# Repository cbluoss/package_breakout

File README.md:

# Chip package breakout board
A simple breakout pcb for different chip packages

Currently supported packages:
* TSOP-I-56
* TSOP-II-54
* SOIC-28
* LFCSP-8
* MSOP-16
* QSOP-24
* DIP-28

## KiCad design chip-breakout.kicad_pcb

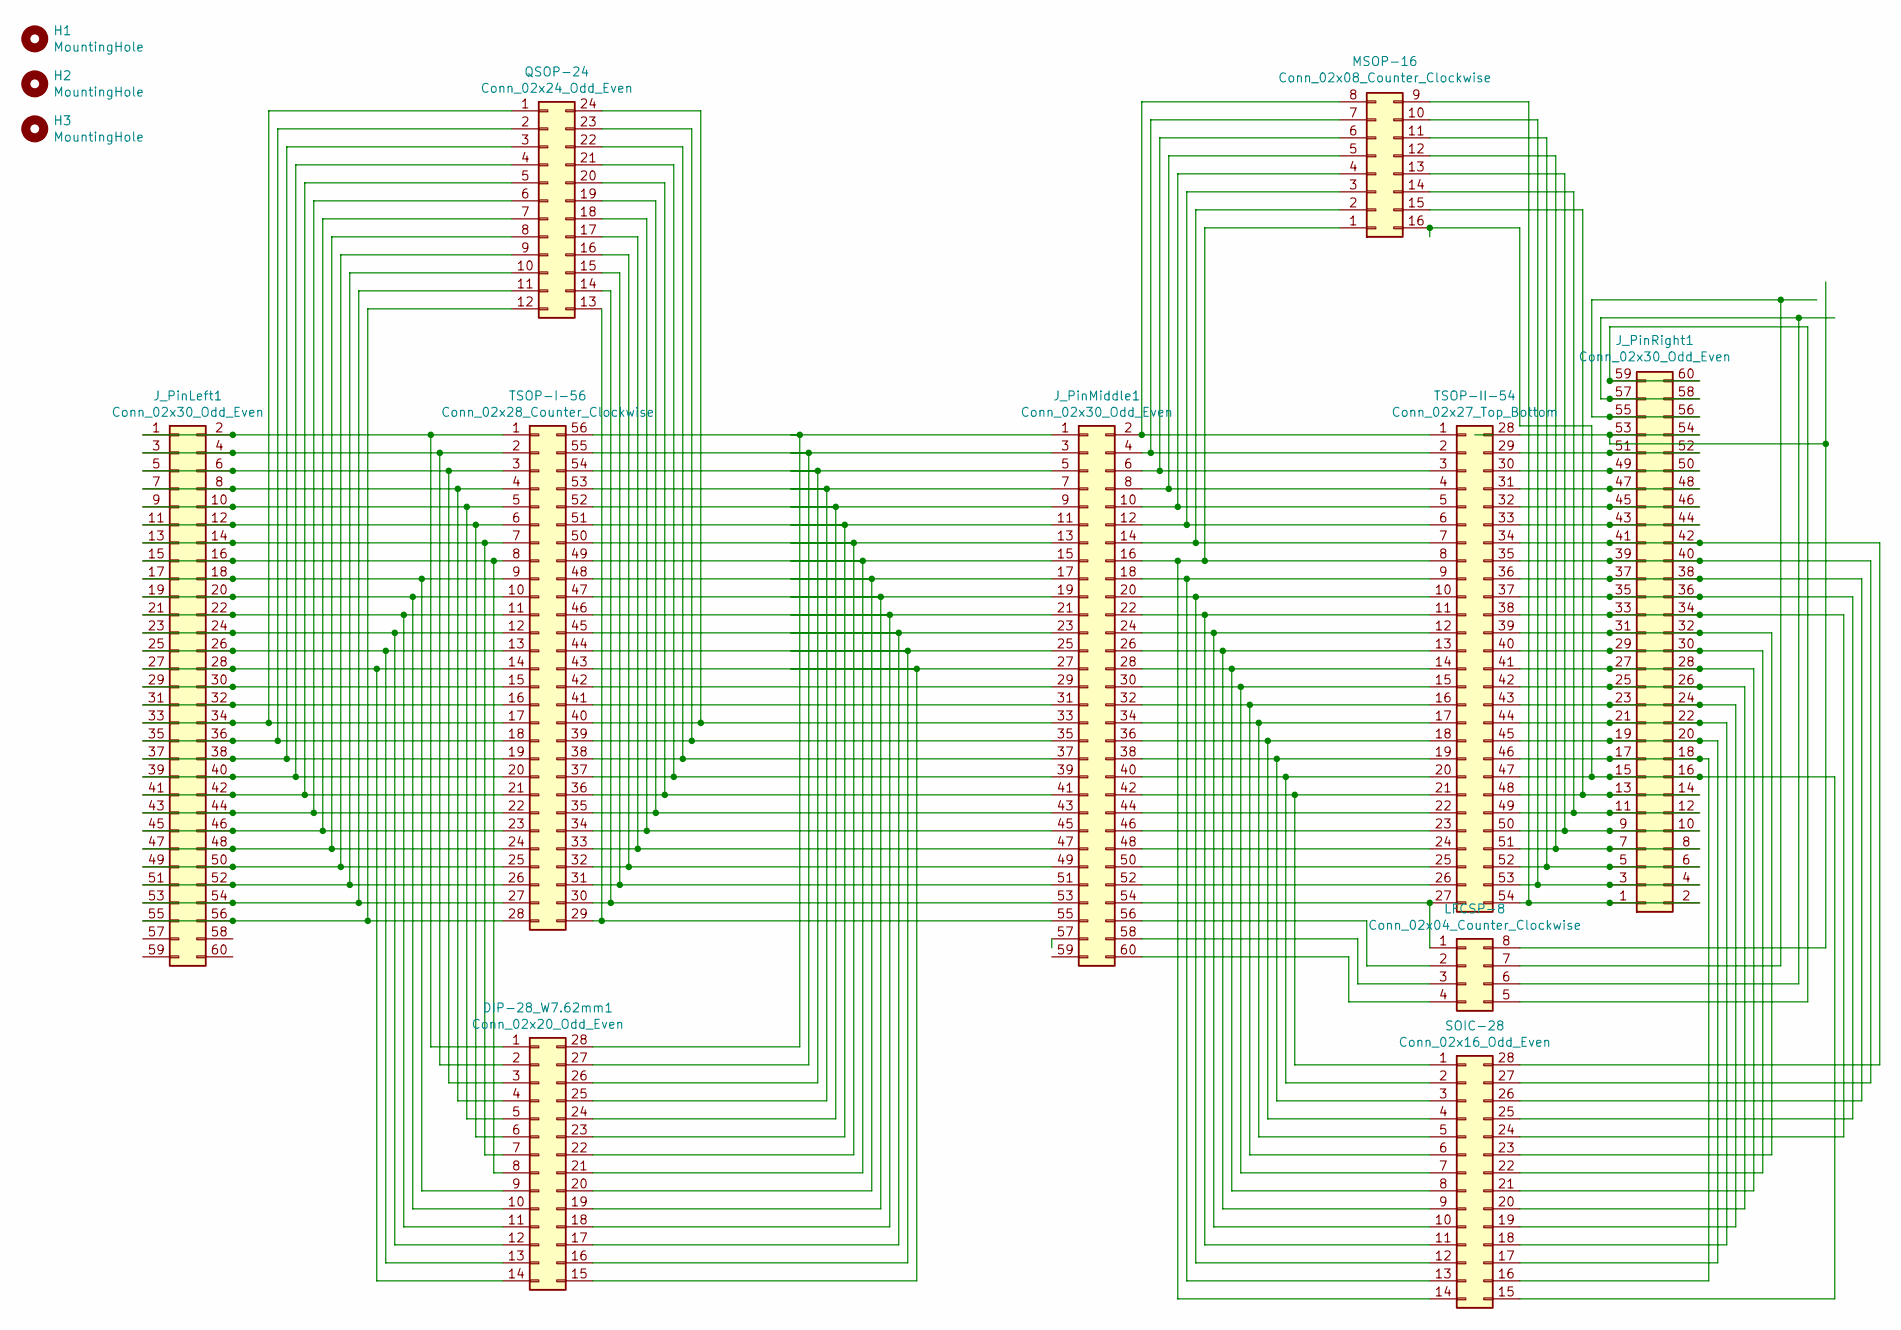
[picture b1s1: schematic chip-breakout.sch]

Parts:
DIP-28_W7.62mm1: Conn_02x20_Odd_Even; DIP-28_W7.62mm_LongPads
H1, H2, H3: MountingHole; MountingHole_3.2mm_M3_ISO7380
J_PinLeft1: Conn_02x30_Odd_Even; PinHeader_2x30_P2.54mm_Vertical
J_PinMiddle1: Conn_02x30_Odd_Even; PinHeader_2x30_P2.54mm_Vertical
J_PinRight1: Conn_02x30_Odd_Even; PinHeader_2x30_P2.54mm_Vertical
LFCSP-8: Conn_02x04_Counter_Clockwise; LFCSP-8-1EP_3x3mm_P0.5mm_EP1.45x1.74mm
MSOP-16: Conn_02x08_Counter_Clockwise; MSOP-16_3x4.039mm_P0.5mm
QSOP-24: Conn_02x24_Odd_Even; QSOP-24_3.9x8.7mm_P0.635mm
SOIC-28: Conn_02x16_Odd_Even; SOIC-28W_7.5x18.7mm_P1.27mm
TSOP-I-56: Conn_02x28_Counter_Clockwise; TSOP-I-56_18.4x14mm_P0.5mm
TSOP-II-54: Conn_02x27_Top_Bottom; TSOP-II-54_22.2x10.16mm_P0.8mm

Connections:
unnamed 0: DIP-28_W7.62mm1.1, J_PinLeft1.1, J_PinLeft1.2, TSOP-I-56.1; also elsewhere on the board
unnamed 1: DIP-28_W7.62mm1.2, J_PinLeft1.3, J_PinLeft1.4, TSOP-I-56.2; also elsewhere on the board
unnamed 2: DIP-28_W7.62mm1.3, J_PinLeft1.5, J_PinLeft1.6, TSOP-I-56.3; also elsewhere on the board
unnamed 3: DIP-28_W7.62mm1.4, J_PinLeft1.7, J_PinLeft1.8, TSOP-I-56.4; also elsewhere on the board
unnamed 4: DIP-28_W7.62mm1.5, J_PinLeft1.9, J_PinLeft1.10, TSOP-I-56.5; also elsewhere on the board
unnamed 5: DIP-28_W7.62mm1.6, J_PinLeft1.11, J_PinLeft1.12, TSOP-I-56.6; also elsewhere on the board
unnamed 6: DIP-28_W7.62mm1.7, J_PinLeft1.13, J_PinLeft1.14, TSOP-I-56.7; also elsewhere on the board
unnamed 7: DIP-28_W7.62mm1.8, J_PinLeft1.15, J_PinLeft1.16, TSOP-I-56.8; also elsewhere on the board
unnamed 8: DIP-28_W7.62mm1.9, J_PinLeft1.17, J_PinLeft1.18, TSOP-I-56.9; also elsewhere on the board
unnamed 9: DIP-28_W7.62mm1.10, J_PinLeft1.19, J_PinLeft1.20, TSOP-I-56.10; also elsewhere on the board
unnamed 10: DIP-28_W7.62mm1.11, J_PinLeft1.21, J_PinLeft1.22, TSOP-I-56.11; also elsewhere on the board
unnamed 11: DIP-28_W7.62mm1.12, J_PinLeft1.23, J_PinLeft1.24, TSOP-I-56.12; also elsewhere on the board
unnamed 12: DIP-28_W7.62mm1.13, J_PinLeft1.25, J_PinLeft1.26, TSOP-I-56.13; also elsewhere on the board
unnamed 13: DIP-28_W7.62mm1.14, J_PinLeft1.27, J_PinLeft1.28, TSOP-I-56.14; also elsewhere on the board
unnamed 14: DIP-28_W7.62mm1.15, J_PinMiddle1.27, TSOP-I-56.43; also elsewhere on the board
unnamed 15: DIP-28_W7.62mm1.16, J_PinMiddle1.25, TSOP-I-56.44; also elsewhere on the board
unnamed 16: DIP-28_W7.62mm1.17, J_PinMiddle1.23, TSOP-I-56.45; also elsewhere on the board
unnamed 17: DIP-28_W7.62mm1.18, J_PinMiddle1.21, TSOP-I-56.46; also elsewhere on the board
unnamed 18: DIP-28_W7.62mm1.19, J_PinMiddle1.19, TSOP-I-56.47; also elsewhere on the board
unnamed 19: DIP-28_W7.62mm1.20, J_PinMiddle1.17, TSOP-I-56.48; also elsewhere on the board
unnamed 20: DIP-28_W7.62mm1.21, J_PinMiddle1.15, TSOP-I-56.49; also elsewhere on the board
unnamed 21: DIP-28_W7.62mm1.22, J_PinMiddle1.13, TSOP-I-56.50; also elsewhere on the board
unnamed 22: DIP-28_W7.62mm1.23, J_PinMiddle1.11, TSOP-I-56.51; also elsewhere on the board
unnamed 23: DIP-28_W7.62mm1.24, J_PinMiddle1.9, TSOP-I-56.52; also elsewhere on the board
unnamed 24: DIP-28_W7.62mm1.25, J_PinMiddle1.7, TSOP-I-56.53; also elsewhere on the board
unnamed 25: DIP-28_W7.62mm1.26, J_PinMiddle1.5, TSOP-I-56.54; also elsewhere on the board
unnamed 26: DIP-28_W7.62mm1.27, J_PinMiddle1.3, TSOP-I-56.55; also elsewhere on the board
unnamed 27: DIP-28_W7.62mm1.28, J_PinMiddle1.1, TSOP-I-56.56; also elsewhere on the board
unnamed: J_PinLeft1.29, J_PinLeft1.30, TSOP-I-56.15
unnamed: J_PinLeft1.31, J_PinLeft1.32, TSOP-I-56.16
unnamed: J_PinLeft1.33, J_PinLeft1.34, QSOP-24.1, TSOP-I-56.17
unnamed: J_PinLeft1.35, J_PinLeft1.36, QSOP-24.2, TSOP-I-56.18
unnamed: J_PinLeft1.37, J_PinLeft1.38, QSOP-24.3, TSOP-I-56.19
unnamed: J_PinLeft1.39, J_PinLeft1.40, QSOP-24.4, TSOP-I-56.20
unnamed: J_PinLeft1.41, J_PinLeft1.42, QSOP-24.5, TSOP-I-56.21
unnamed: J_PinLeft1.43, J_PinLeft1.44, QSOP-24.6, TSOP-I-56.22
unnamed: J_PinLeft1.45, J_PinLeft1.46, QSOP-24.7, TSOP-I-56.23
unnamed: J_PinLeft1.47, J_PinLeft1.48, QSOP-24.8, TSOP-I-56.24
unnamed: J_PinLeft1.49, J_PinLeft1.50, QSOP-24.9, TSOP-I-56.25
unnamed: J_PinLeft1.51, J_PinLeft1.52, QSOP-24.10, TSOP-I-56.26
unnamed: J_PinLeft1.53, J_PinLeft1.54, QSOP-24.11, TSOP-I-56.27
unnamed: J_PinLeft1.55, J_PinLeft1.56, QSOP-24.12, TSOP-I-56.28
unnamed: J_PinMiddle1.2, MSOP-16.8, TSOP-II-54.1
unnamed: J_PinMiddle1.4, MSOP-16.7, TSOP-II-54.2
unnamed: J_PinMiddle1.6, MSOP-16.6, TSOP-II-54.3
unnamed: J_PinMiddle1.8, MSOP-16.5, TSOP-II-54.4
unnamed: J_PinMiddle1.10, MSOP-16.4, TSOP-II-54.5
unnamed: J_PinMiddle1.12, MSOP-16.3, TSOP-II-54.6
unnamed: J_PinMiddle1.14, MSOP-16.2, TSOP-II-54.7
unnamed: J_PinMiddle1.16, MSOP-16.1, SOIC-28.14, TSOP-II-54.8
unnamed: J_PinMiddle1.18, SOIC-28.13, TSOP-II-54.9
unnamed: J_PinMiddle1.20, SOIC-28.12, TSOP-II-54.10
unnamed: J_PinMiddle1.22, SOIC-28.11, TSOP-II-54.11
unnamed: J_PinMiddle1.24, SOIC-28.10, TSOP-II-54.12
unnamed: J_PinMiddle1.26, SOIC-28.9, TSOP-II-54.13
unnamed: J_PinMiddle1.28, SOIC-28.8, TSOP-II-54.14
unnamed: J_PinMiddle1.29, TSOP-I-56.42
unnamed: J_PinMiddle1.30, SOIC-28.7, TSOP-II-54.15
unnamed: J_PinMiddle1.31, TSOP-I-56.41
unnamed: J_PinMiddle1.32, SOIC-28.6, TSOP-II-54.16
unnamed: J_PinMiddle1.33, QSOP-24.24, TSOP-I-56.40
unnamed: J_PinMiddle1.34, SOIC-28.5, TSOP-II-54.17
unnamed: J_PinMiddle1.35, QSOP-24.23, TSOP-I-56.39
unnamed: J_PinMiddle1.36, SOIC-28.4, TSOP-II-54.18
unnamed: J_PinMiddle1.37, QSOP-24.22, TSOP-I-56.38
unnamed: J_PinMiddle1.38, SOIC-28.3, TSOP-II-54.19
unnamed: J_PinMiddle1.39, QSOP-24.21, TSOP-I-56.37
unnamed: J_PinMiddle1.40, SOIC-28.2, TSOP-II-54.20
unnamed: J_PinMiddle1.41, QSOP-24.20, TSOP-I-56.36
unnamed: J_PinMiddle1.42, SOIC-28.1, TSOP-II-54.21
unnamed: J_PinMiddle1.43, QSOP-24.19, TSOP-I-56.35
unnamed: J_PinMiddle1.44, TSOP-II-54.22
unnamed: J_PinMiddle1.45, QSOP-24.18, TSOP-I-56.34
unnamed: J_PinMiddle1.46, TSOP-II-54.23
unnamed: J_PinMiddle1.47, QSOP-24.17, TSOP-I-56.33
unnamed: J_PinMiddle1.48, TSOP-II-54.24
unnamed: J_PinMiddle1.49, QSOP-24.16, TSOP-I-56.32
unnamed: J_PinMiddle1.50, TSOP-II-54.25
unnamed: J_PinMiddle1.51, QSOP-24.15, TSOP-I-56.31
unnamed: J_PinMiddle1.52, TSOP-II-54.26
unnamed: J_PinMiddle1.53, QSOP-24.14, TSOP-I-56.30
unnamed: J_PinMiddle1.54, LFCSP-8.1, TSOP-II-54.27
unnamed: J_PinMiddle1.55, QSOP-24.13, TSOP-I-56.29
unnamed: J_PinMiddle1.56, LFCSP-8.2
unnamed: J_PinMiddle1.58, LFCSP-8.3
unnamed: J_PinMiddle1.60, LFCSP-8.4
unnamed: J_PinRight1.1, J_PinRight1.2, MSOP-16.9, TSOP-II-54.54
unnamed: J_PinRight1.3, J_PinRight1.4, MSOP-16.10, TSOP-II-54.53
unnamed: J_PinRight1.5, J_PinRight1.6, MSOP-16.11, TSOP-II-54.52
unnamed: J_PinRight1.7, J_PinRight1.8, MSOP-16.12, TSOP-II-54.51
unnamed: J_PinRight1.9, J_PinRight1.10, MSOP-16.13, TSOP-II-54.50
unnamed: J_PinRight1.11, J_PinRight1.12, MSOP-16.14, TSOP-II-54.49
unnamed: J_PinRight1.13, J_PinRight1.14, MSOP-16.15, TSOP-II-54.48
unnamed: J_PinRight1.15, J_PinRight1.16, MSOP-16.16, SOIC-28.15, TSOP-II-54.47
unnamed: J_PinRight1.17, J_PinRight1.18, SOIC-28.16, TSOP-II-54.46
unnamed: J_PinRight1.19, J_PinRight1.20, SOIC-28.17, TSOP-II-54.45
unnamed: J_PinRight1.21, J_PinRight1.22, SOIC-28.18, TSOP-II-54.44
unnamed: J_PinRight1.23, J_PinRight1.24, SOIC-28.19, TSOP-II-54.43
unnamed: J_PinRight1.25, J_PinRight1.26, SOIC-28.20, TSOP-II-54.42
unnamed: J_PinRight1.27, J_PinRight1.28, SOIC-28.21, TSOP-II-54.41
unnamed: J_PinRight1.29, J_PinRight1.30, SOIC-28.22, TSOP-II-54.40
unnamed: J_PinRight1.31, J_PinRight1.32, SOIC-28.23, TSOP-II-54.39
unnamed: J_PinRight1.33, J_PinRight1.34, SOIC-28.24, TSOP-II-54.38
unnamed: J_PinRight1.35, J_PinRight1.36, SOIC-28.25, TSOP-II-54.37
unnamed: J_PinRight1.37, J_PinRight1.38, SOIC-28.26, TSOP-II-54.36
unnamed: J_PinRight1.39, J_PinRight1.40, SOIC-28.27, TSOP-II-54.35
unnamed: J_PinRight1.41, J_PinRight1.42, SOIC-28.28, TSOP-II-54.34
unnamed: J_PinRight1.43, J_PinRight1.44, TSOP-II-54.33
unnamed: J_PinRight1.45, J_PinRight1.46, TSOP-II-54.32
unnamed: J_PinRight1.47, J_PinRight1.48, TSOP-II-54.31
unnamed: J_PinRight1.49, J_PinRight1.50, TSOP-II-54.30
unnamed: J_PinRight1.51, J_PinRight1.52, TSOP-II-54.29
unnamed: J_PinRight1.53, J_PinRight1.54, LFCSP-8.8, TSOP-II-54.28
unnamed: J_PinRight1.55, J_PinRight1.56, LFCSP-8.7
unnamed: J_PinRight1.57, J_PinRight1.58, LFCSP-8.6
unnamed: J_PinRight1.59, J_PinRight1.60, LFCSP-8.5

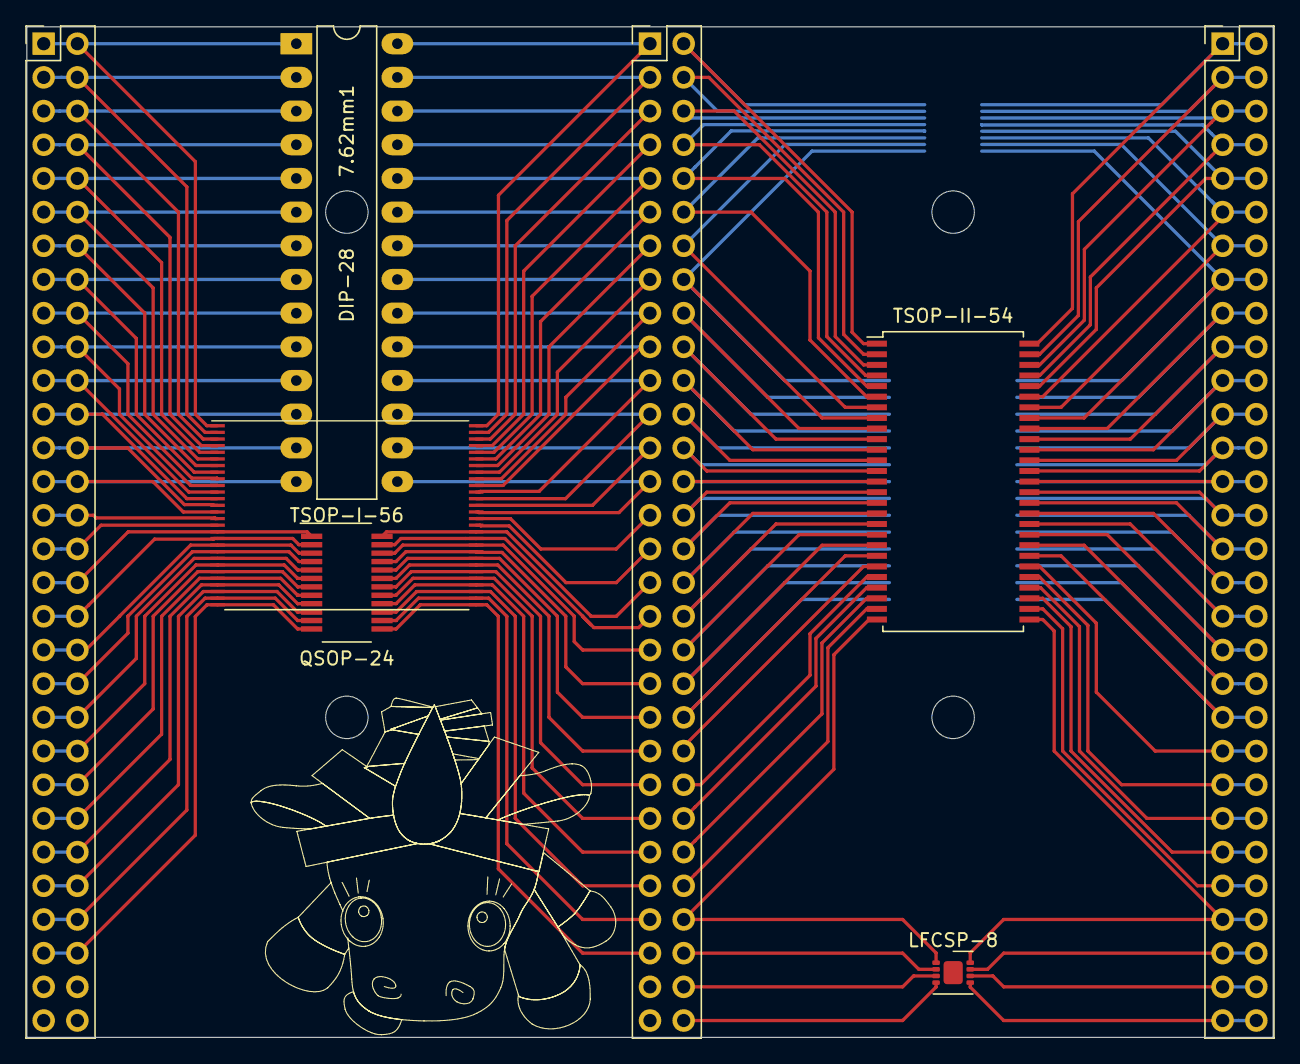
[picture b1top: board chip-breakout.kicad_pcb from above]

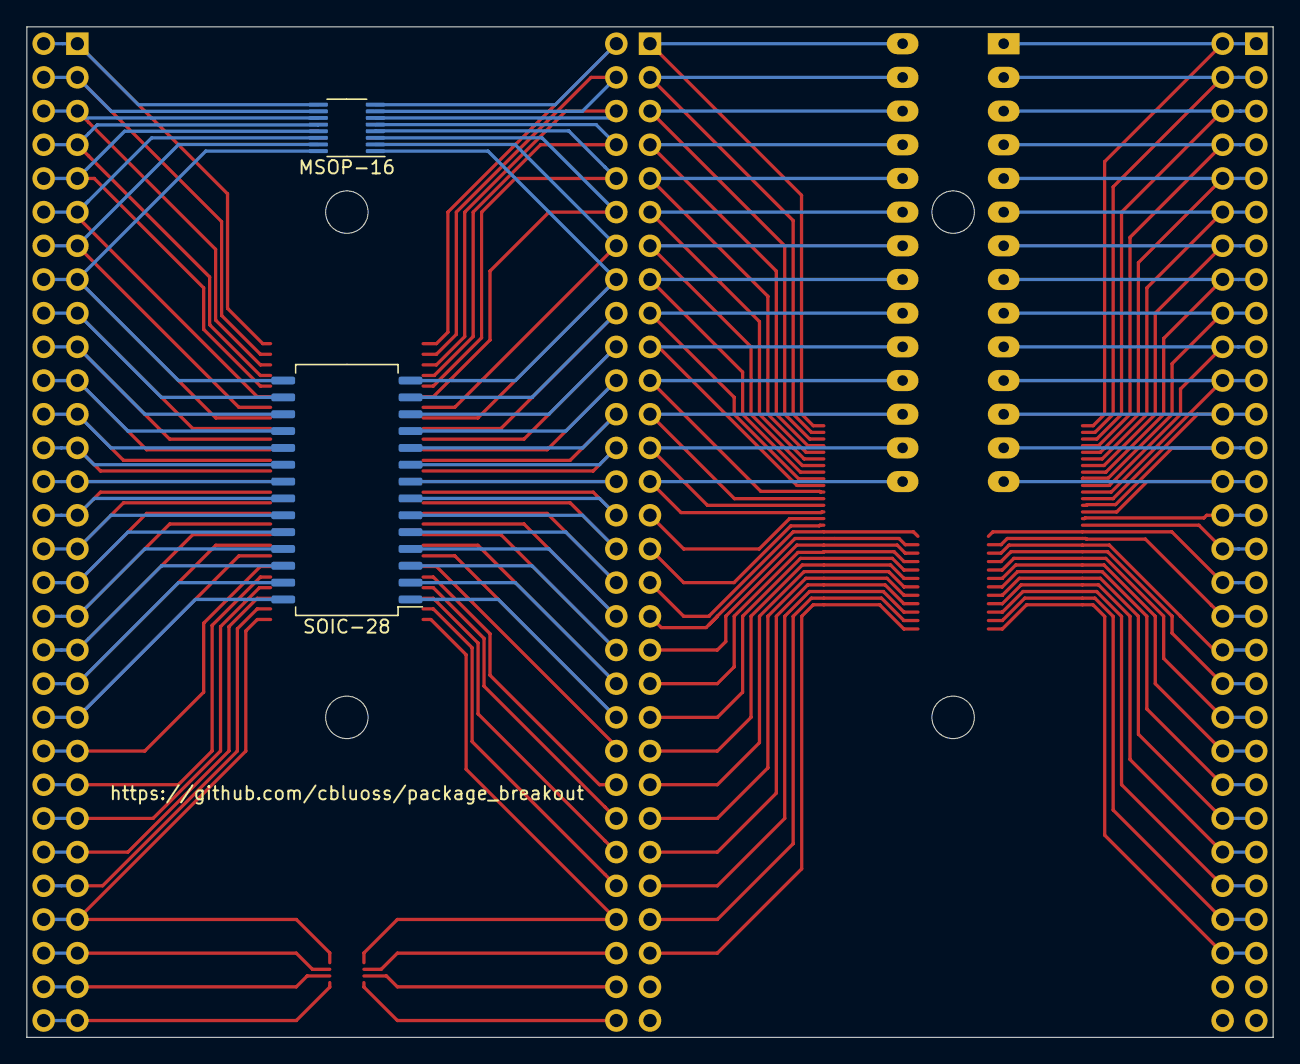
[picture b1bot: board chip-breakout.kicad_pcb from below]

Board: 2 copper layers, 94.0 x 76.2 mm, 14 parts (2 on the bottom side), 116 nets.

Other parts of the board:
DIP-28       7.62mm1: Conn_02x20_Odd_Even; DIP-28_W7.62mm_LongPads
H3#2: MountingHole; MountingHole_3.2mm_M3_ISO7380

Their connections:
unnamed 0: DIP-28 7.62mm1.1; also elsewhere on the board
unnamed 1: DIP-28 7.62mm1.2; also elsewhere on the board
unnamed 2: DIP-28 7.62mm1.3; also elsewhere on the board
unnamed 3: DIP-28 7.62mm1.4; also elsewhere on the board
unnamed 4: DIP-28 7.62mm1.5; also elsewhere on the board
unnamed 5: DIP-28 7.62mm1.6; also elsewhere on the board
unnamed 6: DIP-28 7.62mm1.7; also elsewhere on the board
unnamed 7: DIP-28 7.62mm1.8; also elsewhere on the board
unnamed 8: DIP-28 7.62mm1.9; also elsewhere on the board
unnamed 9: DIP-28 7.62mm1.10; also elsewhere on the board
unnamed 10: DIP-28 7.62mm1.11; also elsewhere on the board
unnamed 11: DIP-28 7.62mm1.12; also elsewhere on the board
unnamed 12: DIP-28 7.62mm1.13; also elsewhere on the board
unnamed 13: DIP-28 7.62mm1.14; also elsewhere on the board
unnamed 14: DIP-28 7.62mm1.15; also elsewhere on the board
unnamed 15: DIP-28 7.62mm1.16; also elsewhere on the board
unnamed 16: DIP-28 7.62mm1.17; also elsewhere on the board
unnamed 17: DIP-28 7.62mm1.18; also elsewhere on the board
unnamed 18: DIP-28 7.62mm1.19; also elsewhere on the board
unnamed 19: DIP-28 7.62mm1.20; also elsewhere on the board
unnamed 20: DIP-28 7.62mm1.21; also elsewhere on the board
unnamed 21: DIP-28 7.62mm1.22; also elsewhere on the board
unnamed 22: DIP-28 7.62mm1.23; also elsewhere on the board
unnamed 23: DIP-28 7.62mm1.24; also elsewhere on the board
unnamed 24: DIP-28 7.62mm1.25; also elsewhere on the board
unnamed 25: DIP-28 7.62mm1.26; also elsewhere on the board
unnamed 26: DIP-28 7.62mm1.27; also elsewhere on the board
unnamed 27: DIP-28 7.62mm1.28; also elsewhere on the board

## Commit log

2021-12-31 including jlcpcb gerbers
